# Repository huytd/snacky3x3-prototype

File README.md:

Second attempt to making keyboard PCB

-----

Update: Two layers autorouting with FreeRouter

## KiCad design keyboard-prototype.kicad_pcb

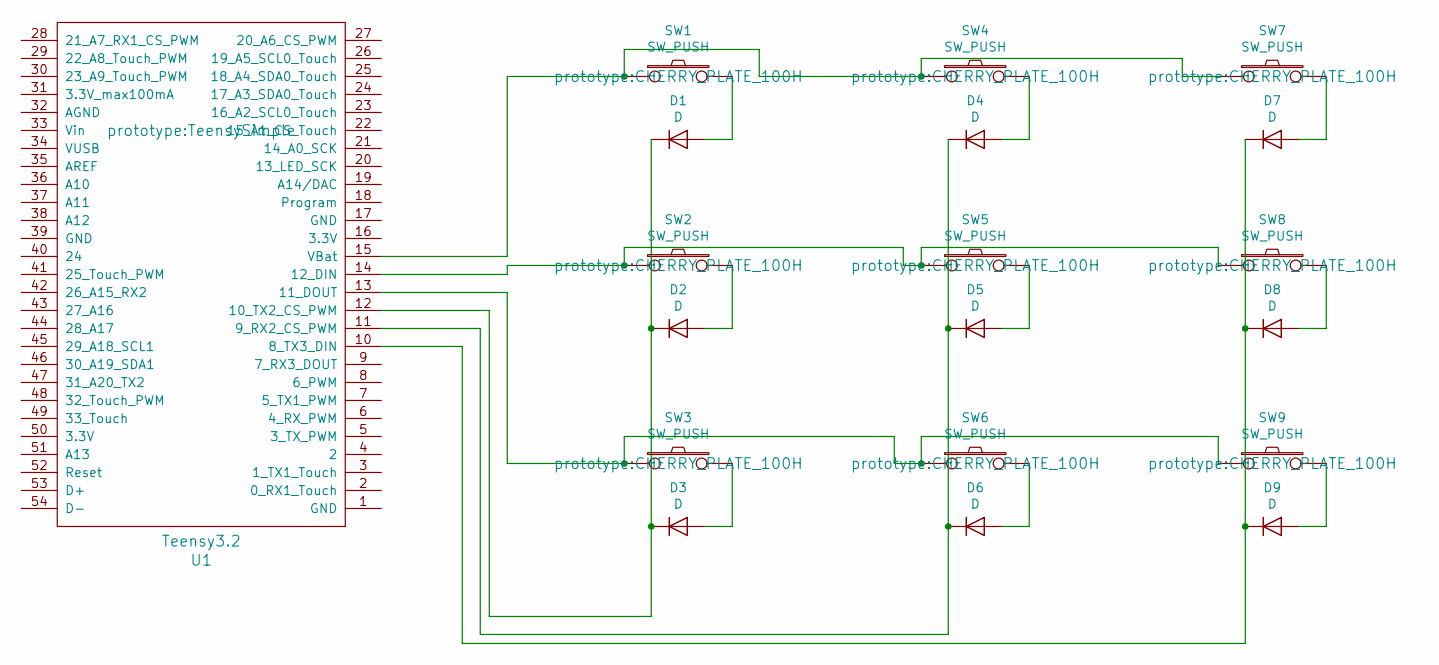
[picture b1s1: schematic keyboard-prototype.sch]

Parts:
D1, D2, D3, D4, D5, D6, D7, D8, D9: D; D_axial
SW1, SW2, SW3, SW4, SW5, SW6, SW7, SW8, SW9: SW_PUSH; CHERRY_PLATE_100H
U1: Teensy3.2; TeensySimple

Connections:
unnamed: D1.1 (K), D2.1 (K), D3.1 (K), U1.12 (10_TX2_CS_PWM)
unnamed: D1.2 (A), SW1.2
unnamed: D2.2 (A), SW2.2
unnamed: D3.2 (A), SW3.2
unnamed: D4.1 (K), D5.1 (K), D6.1 (K), U1.11 (9_RX2_CS_PWM)
unnamed: D4.2 (A), SW4.2
unnamed: D5.2 (A), SW5.2
unnamed: D6.2 (A), SW6.2
unnamed: D7.1 (K), D8.1 (K), D9.1 (K), U1.10 (8_TX3_DIN)
unnamed: D7.2 (A), SW7.2
unnamed: D8.2 (A), SW8.2
unnamed: D9.2 (A), SW9.2
unnamed: SW1.1, SW4.1, SW7.1, U1.15 (VBat)
unnamed: SW2.1, SW5.1, SW8.1, U1.14 (12_DIN)
unnamed: SW3.1, SW6.1, SW9.1, U1.13 (11_DOUT)

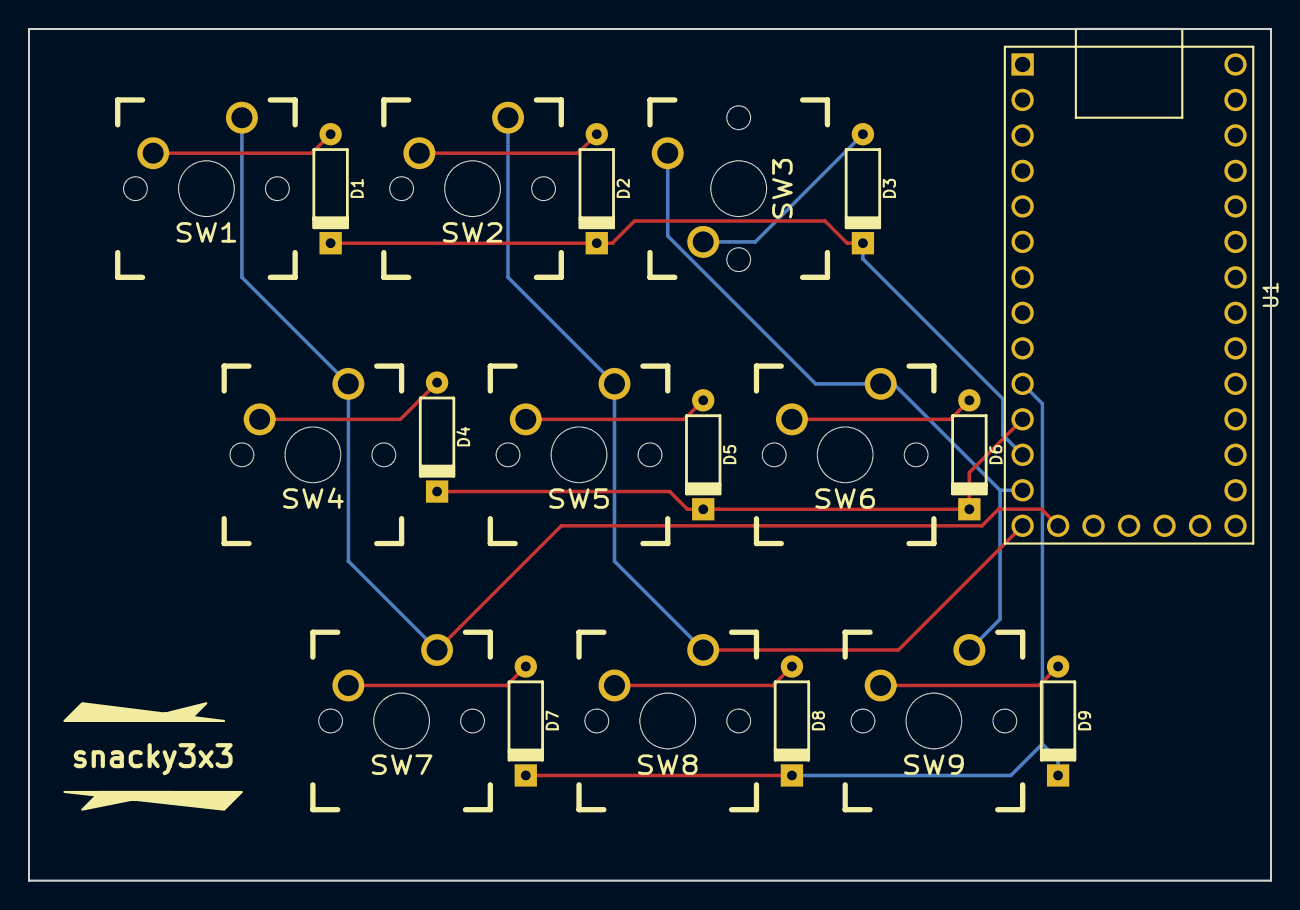
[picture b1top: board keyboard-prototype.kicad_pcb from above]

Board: 2 copper layers, 88.9 x 61.0 mm, 19 parts (0 on the bottom side), 15 nets.

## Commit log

2018-12-20 Autorouting
